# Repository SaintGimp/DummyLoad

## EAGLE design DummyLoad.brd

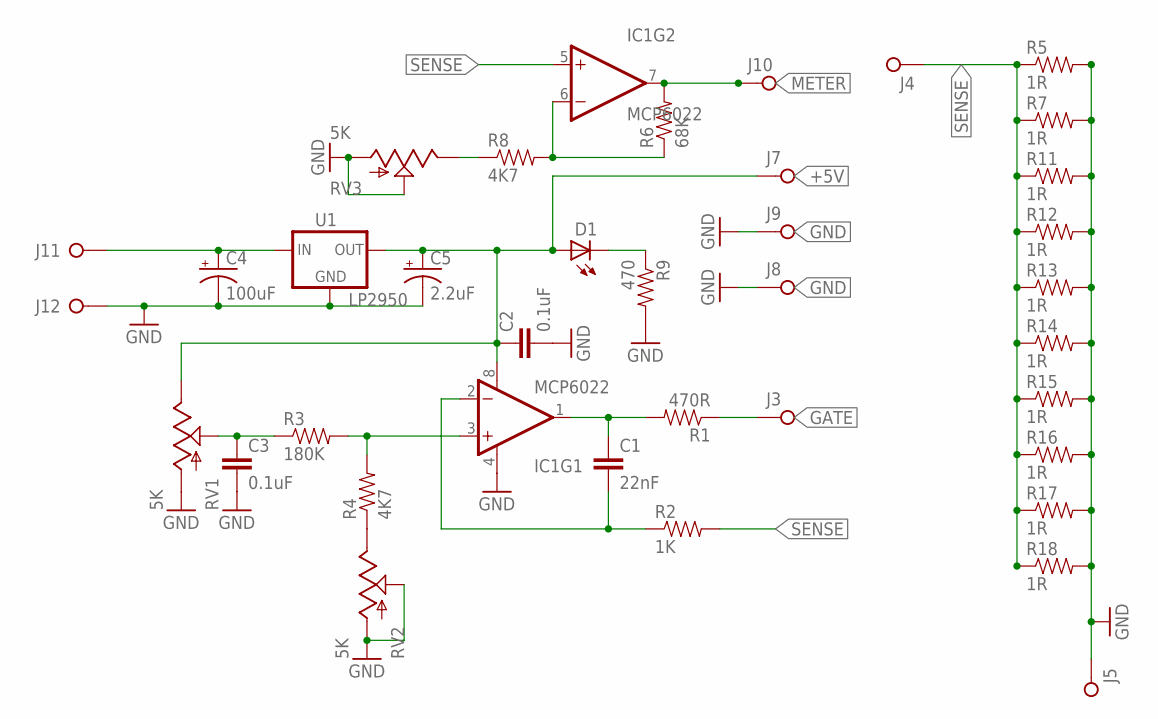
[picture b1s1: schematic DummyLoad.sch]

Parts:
C1: 22nF; CAPACITOR-5MM
C2, C3: 0.1uF; CAPACITOR-5MM
C4: 100uF; CAP-POL-2.5-6
C5: 2.2uF; CAP-POL-2.5-5
D1: LED-5MM; LED5MM
IC1: MCP6022; DIP08
J1: PINHD-1X2; 1X02
J3, J4, J5, J7, J8, J9, J10: PINHD-1X1; 1X01
R1: 470R; AXIAL-7.5MM
R2: 1K; AXIAL-7.5MM
R3: 180K; AXIAL-7.5MM
R4, R8: 4K7; AXIAL-7.5MM
R5, R7, R11, R12, R13, R14, R15, R16, R17, R18: 1R; AXIAL-7.5MM
R6: 68K; AXIAL-7.5MM
R9: 470; AXIAL-7.5MM
RV1: 5K; 1X03
RV2, RV3: 5K; TRIM_POT
U1: LP2950; TO92-INLINE

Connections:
+5V: C2.1, C5.+, D1.A, IC1.8 (V+), J7.1, RV1.3 (E), U1.1 (OUT)
GATE: J3.1, R1.P$1 (1)
GND: C2.2, C3.2, C4.-, C5.-, IC1.4 (V-), J1.2, J5.1, J8.1, J9.1, R5.P$2 (2), R7.P$2 (2), R9.P$2 (2), R11.P$2 (2), R12.P$2 (2), R13.P$2 (2), R14.P$2 (2), R15.P$2 (2), R16.P$2 (2), R17.P$2 (2), R18.P$2 (2), RV1.1 (A), RV2.1 (S), RV2.3 (A), RV3.1 (S), RV3.3 (A), U1.2 (GND)
METER: IC1.7 (OUT), J10.1, R6.P$2 (2)
unnamed: C1.1, IC1.1 (OUT), R1.P$2 (2)
unnamed: C4.+, J1.1, U1.3 (IN)
unnamed: D1.K (C), R9.P$1 (1)
unnamed: C1.2, IC1.2 (-IN), R2.P$1 (1)
unnamed: C3.1, R3.P$1 (1), RV1.2 (S)
unnamed: IC1.6 (-IN), R6.P$1 (1), R8.P$2 (2)
unnamed: R4.P$1 (1), RV2.2 (E)
unnamed: R8.P$1 (1), RV3.2 (E)
unnamed: IC1.3 (+IN), R3.P$2 (2), R4.P$2 (2)
SENSE: IC1.5 (+IN), J4.1, R2.P$2 (2), R5.P$1 (1), R7.P$1 (1), R11.P$1 (1), R12.P$1 (1), R13.P$1 (1), R14.P$1 (1), R15.P$1 (1), R16.P$1 (1), R17.P$1 (1), R18.P$1 (1)

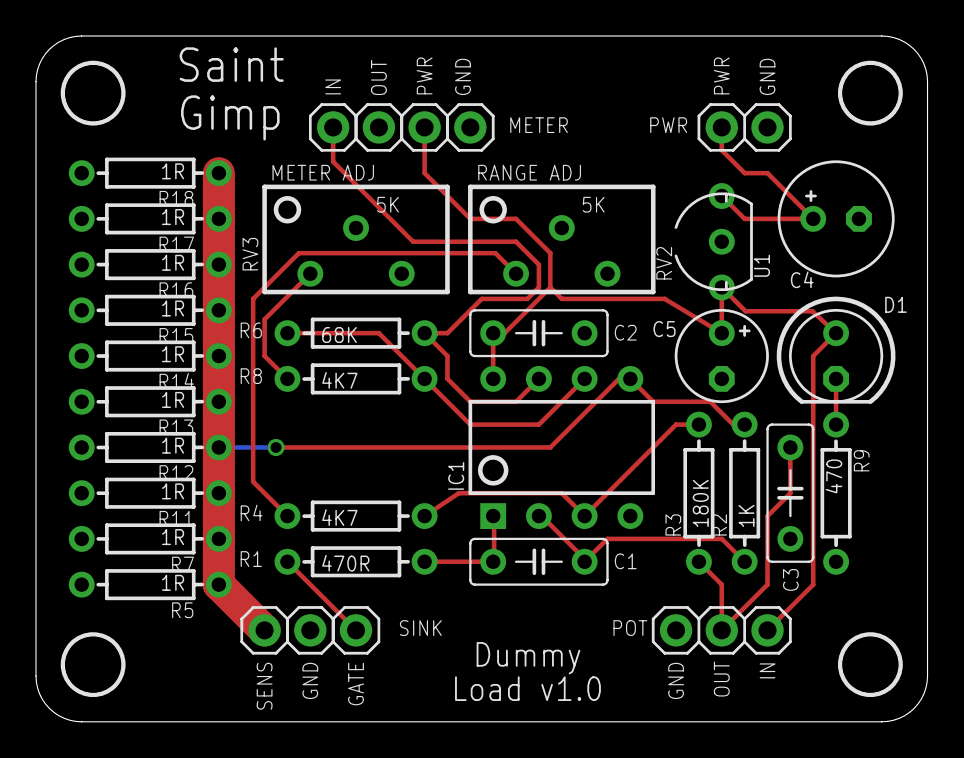
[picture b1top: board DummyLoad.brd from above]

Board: 2 copper layers, 49.5 x 38.1 mm, 40 parts (0 on the bottom side), 14 nets.

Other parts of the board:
U$1, U$2, U$3, U$4: MOUNTING-HOLE-3.2MM

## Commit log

2015-03-22 initial commit, WIP
2015-03-25 Rough layout
2015-03-26 Second layout pass
2015-03-26 Add silk screen
2015-11-06 Tweak values
2015-11-14 Clean up layout
2016-10-11 Design updates
2016-10-11 Add sensor resistor array to board
2016-10-29 Tweaked layout
